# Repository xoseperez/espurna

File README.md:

# ESPurna Firmware

ESPurna ("spark" in Catalan) is a custom firmware for ESP32 and ESP8285/ESP8266 based smart switches, lights and sensors.
It uses the Arduino Core for ESP32 / ESP8266 frameworks and a number of 3rd party libraries.
This fork adds the [ESP32 and Beken BK72xx ports](#this-fork) and [a page per architecture](#architectures) with the boards run on it; the badges right below refer to the original upstream project.

<br />

---

## This fork

This fork is maintained by **@igorufox**. ESPurna itself is the work of Xose Pérez (**@xoseperez**), Max Prokhorov (**@mcspr**) and the upstream contributors, credited below.

It lives in the [`esp32-port`](https://github.com/igorufox/espurna/tree/esp32-port) branch: three architectures from the same source, a few generic images per chip instead of per-board builds (the board is picked after flashing, see [Picking the board](#picking-the-board)), and updates from the GitHub releases in the WebUI.

- **ESP8266 / ESP8285** (Arduino core 3.1.2, NONOS SDK 3.0.5): four generic images instead of the 216 per-board builds, a two-step update through a mini image on 1 MB boards, lwIP and module memory tuned so that the WebUI and uploads fit in the heap, AC mains wall-switch inputs; builds in [`code/platformio.ini`](code/platformio.ini), [esp8266/README.md](esp8266/README.md);
- **ESP32** (Arduino-ESP32 core 3 / ESP-IDF 5 via [pioarduino](https://github.com/pioarduino/platform-espressif32), PlatformIO Core 6.2 or newer; Matter On/Off plugs; safeboot flash layout with Tasmota's offsets, [`code/esp32_4mb_safeboot.csv`](code/esp32_4mb_safeboot.csv), and an own safeboot image, [`code/safeboot-app`](code/safeboot-app)), code under [`code/espurna/arch/esp32`](code/espurna/arch/esp32), [esp32/README.md](esp32/README.md);
- **Beken BK7231N** (Tuya CB2S / CB3S / CBU and compatible modules, Tuya or Quectel bootloader) through [LibreTiny](https://docs.libretiny.eu/), Matter On/Off plugs, code under [`code/espurna/arch/beken`](code/espurna/arch/beken), builds in [`code/platformio_beken.ini`](code/platformio_beken.ini), [beken/README.md](beken/README.md).

How updates work on each chip, the releases and CI: [docs/updates.md](docs/updates.md).

### Architectures

One source, three architectures; every one has a page with its images, the boards run on it, their pages and its
nuances. Boards run on the generic image of their chip; pins come from the device template (*ADMIN → Device Template*)
or the settings, not from the build.

| Architecture | Images | Boards run on it | Page |
|--------------|--------|------------------|------|
| **ESP8266 / ESP8285** | `esp8266-1m`, `-1m-light`, `-1m-sensor`, `-4m` (+ the mini) | Sonoff Basic, Sonoff Mini R1/R2, Moes MS-104B, HW-622, LC-Tech ESP-12F relay x2 and x4 | [esp8266/README.md](esp8266/README.md) |
| **ESP32** | `esp32-matter`, `esp32-matter-nspanel` (+ the safeboot) | LC-Tech ESP32 relay x2, Sonoff MINIR4, Sonoff NSPanel | [esp32/README.md](esp32/README.md) |
| **Beken BK7231N** | `beken-matter` (+ two UART images) | Tuya TYWRA-RF (CB3S), Tuya 4-gang (CBU), Sparkleiot Mini (XH-CB2S), in-wall relay 86-TDQ (CB2S), MOES MS-104B Matter (CBU) | [beken/README.md](beken/README.md) |

How updates work on each chip, the releases and CI: [docs/updates.md](docs/updates.md).

### Download

Every push to `esp32-port` is built by [GitHub Actions](https://github.com/igorufox/espurna/actions/workflows/esp32.yml) and published as one [release](https://github.com/igorufox/espurna/releases/latest) for all chips, tag `esp32-YYMMDD-<sha7>`; the newest 5 are kept. The same files with their SHA-256 are listed in [`firmware.json`](https://igorufox.github.io/espurna/firmware.json) on GitHub Pages, which the WebUI reads. The latest image is always at `https://github.com/igorufox/espurna/releases/latest/download/espurna-<image>...`, e.g. [espurna-esp32-matter.bin](https://github.com/igorufox/espurna/releases/latest/download/espurna-esp32-matter.bin). Which image and how to flash it the first time: the page of the architecture.

### Updating

WebUI, *ADMIN*, OTA: *Upgrade* with a file as before, or *From GitHub*, *Show releases*: the kept releases with the files of the image the board runs, *Install*. The WebUI lists the steps ahead and goes through them by itself; the board restarts during the install.

- **ESP32**: through the safeboot, which downloads the image's `.bin` itself and writes its ESPurna part; two-slot boards are migrated on the way.
- **Beken**: the browser uploads `espurna-beken-matter.bin`, the board writes the part for its bootloader; on 2 MiB Tuya boards in up to three uploads of the same file, because the Matter code lives in the update partition ([how](docs/updates.md#2-mib-tuya-boards-where-matter-lives)).
- **ESP8266**: one upload on the 4 MB layout; on 1 MB boards the mini first, which downloads the compressed full image from GitHub Pages.

Details, limits and what happens when an install stops half-way: [docs/updates.md](docs/updates.md).

### Picking the board

WebUI, *ADMIN*, *Device Template*: type the name (e.g. `sonoff mini`, `shelly 1pm`, `ms-104b`) and *Apply*. The list is downloaded by the browser at that moment from [templates.blakadder.com](https://templates.blakadder.com) (Tasmota templates, ESP8266 / ESP32), [OpenBeken](https://openbekeniot.github.io/webapp/devicesList.html) (Beken) and [igorufox/espurna-devices](https://github.com/igorufox/espurna-devices) (*ESPurna devices*, results marked `[github]`); nothing is stored here. AC mains wall switches are marked afterwards on the RELAYS panel, per button. Your own board: [add a template](https://templates.blakadder.com/new.html) to the Tasmota list, the `devices.json` of [openbekeniot/webapp](https://github.com/openbekeniot/webapp) for Beken, or an entry of espurna-devices.

**ESPurna devices.** [`devices.json`](https://github.com/igorufox/espurna-devices) holds every ESP8266 board of [`hardware.h`](code/espurna/config/hardware.h) (generated by [`code/scripts/boards_to_devices.py`](code/scripts/boards_to_devices.py), most of them not verified on hardware since the move to generic images) and the no-name boards that are in no other list, such as the [CBU 4-gang module](beken/cbu-4gang.md) and the [Sparkleiot Mini](beken/sparkleiot-mini.md). Another list: the `webTplUrl` setting, *Own device list* in the same panel. A board set up by hand is turned into an entry with *Export this device as a template*: only relay / button / LED / UART / RF pins, button actions and the board names are taken, never Wi-Fi, MQTT, passwords or topics, and only those keys are ever applied from the list.

### Build from source

```
cd code
pio run -e esp8266-1m                                # ESP8266, see esp8266/README.md
pio run -d safeboot-app                              # ESP32: the safeboot first, then
pio run -c platformio_esp32.ini -e esp32-generic
py -3 -m platformio run -c platformio_beken.ini -e beken-bk7231n   # Beken
```

Details per architecture on its page.

---

# Original ESPurna README

Everything below is the upstream [xoseperez/espurna](https://github.com/xoseperez/espurna) README and describes ESP8266 builds.

## Collaborators (upstream)

Since November 2018, Max Prokhorov (**@mcspr**) is also actively working as a collaborator of the project. 

## Contributors (upstream)

**Without your help this project would not be possible**. I (**@xoseperez**) simply can't spend all the time I wish on ESPurna but luckily I receive a lot of contributions, bug fixes, enhancement suggestions,... from people all around the world. I would like to thank each and every one of you. The [contributors](https://github.com/xoseperez/espurna/graphs/contributors) page shows the ones that have done a PR in the past, but I also get contributions in the issues, by email or via the [gitter ESPurna channel](https://gitter.im/tinkerman-cat/espurna), those I also want to thank.

**Thank you all very much**.

## Notice

> Ladies and gentlemen in the embedded world, use [PlatformIO](https://platformio.org/). If I could offer you only one tip for the future, [PlatformIO](https://platformio.org/) would be it.

> Please use the [gitter ESPurna channel](https://gitter.im/tinkerman-cat/espurna) for support and questions, you have better chances to get fast answers from me or other ESPurna users. Open an issue here only if you feel there is a bug or you want to request an enhancement. Thank you.

> Process of building ESPurna from source is documented in the Wiki:  
[Using PlatformIO IDE for VSCode](https://github.com/xoseperez/espurna/wiki/Build-and-update-from-Visual-Studio-Code-using-PlatformIO)  
[Using PlatformIO CLI](https://github.com/xoseperez/espurna/wiki/PlatformIO)  
[Using Arduino IDE](https://github.com/xoseperez/espurna/wiki/ArduinoIDE)  

## Features

* *KRACK* vulnerability free (when built with Arduino Core >= 2.4.0)
* Support for **multiple ESP8266-based boards** ([check list](https://github.com/xoseperez/espurna/wiki/Hardware))
* Power saving options
* Wifi **AP Mode** or **STA mode**
    * Supports static IP
    * Up to 5 different networks can be defined
    * Scans for strongest network if more than one defined (also available in web UI)
    * Handles correctly multiple AP with the same SSID
    * Defaults to AP mode (also available after double clicking the main button)
    * Support for **WPS** and **Smart Config** (not available in default builds)
* Network visibility
    * Supports mDNS (service reporting and metadata) both server mode and client mode (.local name resolution)
    * Supports NetBIOS, LLMNR and Netbios (when built with Arduino Core >= 2.4.0) and SSDP (experimental)
* Switch management
    * Support for **push buttons** and **toggle switches**
    * Support for **digital** and [**analog**](https://en.wikipedia.org/wiki/Resistor_ladder) buttons
    * Configurable **status on boot** per switch (always ON, always OFF, same as before or toggle)
    * Support for **pulse mode** per switch (normally ON or normally OFF) with configurable time
    * Support for **relay synchronization** (all equal, only one ON, one and only on ON)
    * Support for **MQTT groups** to sync switches between devices
    * Support for **delayed ON/OFF**
    * Support for **latched relays**
* **MQTT** enabled
    * **SSL/TLS support** (not on regular builds, see [#64](https://github.com/xoseperez/espurna/issues/64) and [#1465](https://github.com/xoseperez/espurna/issues/1465))
    * Switch on/off and toggle relays, group topics (sync relays between different devices)
    * Report button event notifications
    * Enable/disable pulse mode
    * Change LED notification mode
    * Remote reset the board
    * Fully configurable in webUI (broker, user, password, QoS, keep alive time, retain flag, client ID)
* **Scheduler** to automatically turn on, off or toggle any relay at a given time and day, also change light intensity for dimmers
* **Alexa** integration using the [FauxmoESP Library](https://bitbucket.org/xoseperez/fauxmoesp)
* [**Google Assistant**](http://tinkerman.cat/using-google-assistant-control-your-esp8266-devices/) integration using IFTTT and Webhooks (Google Home, Allo)
* [**Domoticz**](https://domoticz.com/) integration via MQTT
* [**Home Assistant**](https://home-assistant.io/) integration
    * Support for switches (on/off)
    * Support for lights (color, brightness, on/off state)
    * Supports MQTT auto-discover feature (switches, lights and sensors)
    * Integration via MQTT Discover or copy-pasting configuration code
* [**InfluxDB**](https://www.influxdata.com/) integration via HTTP API
* [**Prometheus**](https://prometheus.io/) metrics integration via HTTP API
* [**Thingspeak**](https://thingspeak.com/) integration via HTTP API (HTTPS available for custom builds)
* **Sonoff RF Bridge** support
    * Multiple virtual switches (tested with up to 16)
    * MQTT-to-RF two-way bridge (no need to learn codes)
    * Support for [https://github.com/Portisch/RF-Bridge-EFM8BB1](https://github.com/Portisch/RF-Bridge-EFM8BB1) custom firmware
    * Support for [direct control of the encoder/decoder bypassing the EFM8BB1](https://github.com/xoseperez/espurna/wiki/Hardware-Itead-Sonoff-RF-Bridge---Direct-Hack)
* Support for [different **sensors**](Sensors)
    * Environment
        * **DHT11 / DHT12 / DHT22 / DHT21 / AM2301 / Itead's SI7021**
        * **BMP180**, **BMP280** and **BME280** pressure, humidity (BME280) and temperature (BMP280 & BME280) sensor by Bosch
        * **BME680** pressure, humidity, temperature and gas sensor by Bosch with support for Bosch's proprietary library BSEC for accurate Indoor Air Quality (IAQ) monitoring (⚠️ [learn more](https://github.com/xoseperez/espurna/wiki/Sensors#bme680-environmental-sensor))
        * **TMP35** and **TMP36** analog temperature sensors
        * **MAX6675** temperature sensor
        * **NTC** temperature sensors
        * **SI7021** temperature and humidity sensor
        * **SHT3X** temperature and humidity sensor over I2C (Wemos shield)
        * **AM2320** temperature and humidity sensor over I2C
        * **Dallas OneWire sensors** like the DS18B20
        * **MHZ19** CO2 sensor
        * **T6613** CO2 sensor
        * **MICS2710** CO2 & NO2 sensor
        * **MICS5525** CO & CO2 sensor
        * **SenseAir S8** CO2 sensor
        * **PMSX003/PMS5003T/ST** dust sensors
        * **SDS011** dust sensor
        * **BH1750** luminosity sensor
        * **GUVAS12SD** UV sensor
        * **VEML6075** UV Sensor
        * **EZO pH Circuit**
        * **Geiger counter** by RH Electronics
        * **HC-SR04**, **SRF05**, **SRF06**, **DYP-ME007**, **JSN-SR04T** & **Parallax PING)))™** distance sensors
        * **VL53L1X** distance sensor
        * **MAX6675** K-thermocouple-to-digital converter
        * **NTC** thermistor
        * **LDR** light-dependent resistor sensor
    * Power monitoring
        * **HLW8012** using the [HLW8012 Library](https://bitbucket.org/xoseperez/hlw8012) (Sonoff POW)
        * **CSE7766** and **CSE7759B** power monitor chips
        * **HJL-01** and **BL0937** power monitor chips
        * Non-invasive **current sensor** using **internal ADC** or **ADC712** or **ADC121** or **ADS1015** / **ADS1115**
        * **V9261F** power monitor chip
        * **PZEM0004T**  power monitor board
        * **ECH1560** power monitor chip
        * **ADE7953** power monitor chip
    * Raw **analog** and **digital** sensors
    * Simple **pulse counter** with **event triggering** option
    * Support for (almost) any UART based sensor via the **UART-to-MQTT module**
    * Support for different units (Fahrenheit or Celsius, Watts or Kilowatts, Joules or kWh)
* Support for LED lights
    * MY92XX-based light bulbs and PWM LED strips (dimmers) up to 5 channels (RGB, cold white and warm white, for instance)
    * Support for CCT lights
    * RGB and HSV color codes supported
    * Manage channels individually
    * Temperature color supported (in [mired](https://en.wikipedia.org/wiki/Mired) and [kelvin](https://en.wikipedia.org/wiki/Color_temperature)) via MQTT / REST API
    * Flicker-free PWM management
    * Soft color transitions
    * Color synchronization between light using MQTT
    * Option to have separate switches for each channel
* Support for simple 433MHz RF receivers
* Support for UART-to-MQTT bidirectional bridge
* Fast asynchronous **HTTP Server** and cool **Web User Interface**
    * Configurable port
    * Basic authentication
    * Web-based configuration
    * Relay switching and sensor data from the web interface
    * Handle color, brightness, and white/warm channels for lights
    * Websockets-based communication between the device and the browser
    * Backup and restore settings option
    * Upgrade firmware from the web interface
    * Works great behind a [secured reverse proxy](http://tinkerman.cat/secure-remote-access-to-your-iot-devices/)
* **REST API** (enable/disable from web interface)
    * GET and PUT relay status (including pulses)
    * Change light color (for supported hardware)
    * GET sensor data (power, current, voltage, temperature and humidity) depending on the available hardware
    * Works great behind a secured reverse proxy
* **RPC API** (enable/disable from web interface)
    * Remote reset the board
* **RPN Rules - on-device automation**
    * Relays on/off/toggle
    * Lights control
    * Publish / subscribe to MQTT
    * RF receiver integration
* **Over-The-Air** (OTA) updates even for 1Mb boards
    * Manually from PlatformIO or Arduino IDE
    * Automatic updates through the [NoFUSS Library](https://bitbucket.org/xoseperez/nofuss)
    * Update from web interface using pre-built images
* **Command line configuration**
    * Change configuration
    * Run special commands
* **Telnet support**
    * Enable/disable via the web UI
    * Shows debug info and allows to run terminal commands
* **NTP** for time synchronization
    * Supports worldwide time zones
    * Compatible with DST (based on [POSIX TZ variable](https://www.gnu.org/software/libc/manual/html_node/TZ-Variable.html) support)
* **Unstable system check**
    * Detects unstable system (crashes on boot continuously) and defaults to a stable system
    * Only WiFi AP, OTA and Telnet available if system is flagged as unstable
* Configurable LED notifications based on WiFi status, relays status or MQTT messages.
* Button interface
    * Click to toggle relays
    * Double click to enter AP mode (only main button)
    * Long click (>1 second) to reboot device (only main button)
    * Extra long click (>10 seconds) to go back to factory settings (only main button)
    * Specific definitions for touch button devices (ESPurna Switch, Sonoff Touch & T1)
* Configuration stored in different flash sectors to prevent data loss and corruption
* **Garland** Implementing garland using WS2812 leds
    * 12 animation modes (include start animation)
    * Web control for:
        * ON/OFF, brightness, speed
    * MQTT control:
        * ON/OFF, brightness, speed
        * Animation queue
        * Animation sequence

## Notices

---
> **2018-04-08**<br />
> Please use [gitter](https://gitter.im/tinkerman-cat/espurna) for support and questions, you have better chances to get fast answers by me or other ESPurna users. Open an issue here only if you feel there is a bug or you want to request an enhancement. Thank you.

---
> **2018-03-09**<br />
> Default branch in GitHub is now the development branch "dev".<br>
> The stable branch (the one used to create the [binary releases](https://github.com/xoseperez/espurna/releases)) is "[master](https://github.com/xoseperez/espurna/tree/master)".

---
> **2018-01-24**<br />
> This repository has been migrated from Bitbucket to GitHub. There were a number of reason to migrate the repository to GitHub. I like Bitbucket and I'm still using it for a lot of projects, but ESPurna has grown and its community as well. Some users have complain about Bitbucket not being enough community-focused. This change is mainly aimed to use a platform with greater acceptance on the open-source community and tools better suited to them (to you), like the possibility to contribute to the documentation in an easy way.
>
>What happened with all the info in Bitbucket? Well, most of it has been ported to GitHub, albeit with some quirks:
>
>* **Code** has, of course been migrated completely
>* **Issues** are all on GitHub already **but** all issues and comments show up as reported by me. The original reporter is referenced inside the body of the issue (or comment) with a link to his/her profile at Bitbucket and a link to his/her profile at GitHub if it happens to be the same username. I **suggest all reporters to subscribe to the issues they originally filed** (search for your BitBucket username to list them).
>* **Pull requests** historic has not been migrated. At the moment of the migration all pull-requests have been either merged or declined. Of course, those PR merged are in the code base, but the historic and comments in the PR pages will be lost.
>* **Documentation** it's on it way, first step will be to migrate existing wiki, maybe with a new TOC structure
>* **Watchers**, **Forks**, I'm afraid they are all gone. Visit the new repo home and click on the "Watch" button on the top right. And as you do it click also on the "Star" button too :)
>
>I apologize for any inconvenience this migration may have caused. I have decided to do it the hard way.

---
> **2018-01-11**<br />
> As of current version (1.12.0) ESPurna is tested using Arduino Core 2.3.0 and it's meant to be built against that version.

---
> **2017-08-26**<br />
> Since version 1.9.0 the default **MQTT topics for commands have changed**. They all now end with "/set". This means you will have to change your controller software (Node-RED or alike) to send messages to -for instance- "/home/living/light/relay/0/set". The device will publish its state in "/home/living/light/relay/0" like before.

---
> **2017-07-24**<br />
> Default flash layout changed in 1.8.3, as an unpredicted consequence devices will not be able to persist/retrieve configuration if flashed with 1.8.3 via **OTA** from **PlatformIO**. Please check issue [#187](https://github.com/xoseperez/espurna/issues/187).

---

## Contribute

There are several ways to contribute to ESPurna development. You can contribute to the repository by doing:

* Pull requests (fixes, enhancements, new features... are very welcome)
* Documentation (I reckon I'm bad at it)
* Testing (filing issues or help resolving them, they take a lot of time and sometimes I don't have the required hardware to test them all)

And of course you can always buy me a beer, coffee, tea,... via the donation button below.

## Documentation

For more information please refer to the [ESPurna Wiki](https://github.com/xoseperez/espurna/wiki).

## Supported hardware

Here is the list of supported hardware. For more information please refer to the [ESPurna Wiki Hardware page](https://github.com/xoseperez/espurna/wiki/Hardware), search for wiki pages starting with *Hardware-...*, or search throught [our build configuration files with hardware presets](https://github.com/xoseperez/espurna/blob/dev/code/espurna/config/hardware.h).

### Power monitoring devices

||||
|---|---|---|
||||
|**Blitzwolf BW-SHP6**|**[Blitzwolf BW-SHP2](https://github.com/xoseperez/espurna/wiki/Hardware-BLITZWOLF-BW-SHP2)**<br />(also by Coosa, Gosund, HomeCube, Teckin)|**Blitzwolf BW-SHP5**|
||||
|**[Power meters based on V9261F](https://github.com/xoseperez/espurna/wiki/Hardware-Generic-V9261F)**|**[Itead Sonoff POW](https://github.com/xoseperez/espurna/wiki/Hardware-Itead-Sonoff-POW)**|**[Itead Sonoff POW R2](https://github.com/xoseperez/espurna/wiki/Hardware-Itead-Sonoff-POW-R2)**|
||||
|**[Itead Sonoff S31](https://github.com/xoseperez/espurna/wiki/Hardware-Itead-Sonoff-S31)**|**Smartlife (NETVIP) Mini Smart Socket**|**Teckin SP20**|
||||
|**Digoo NX SP202**|**Vanzavanzu Smart WiFi Plug Mini**|**Hykker Smart Home Power Plug**|

### Embedded switches

||||
|---|---|---|
||||
|**[Itead Sonoff Basic (including R2 and R3)](https://github.com/xoseperez/espurna/wiki/Hardware-Itead-Sonoff-Basic)**|**[Itead Sonoff Dual/Dual R2](https://github.com/xoseperez/espurna/wiki/Hardware-Itead-Sonoff-Dual)**|**[Itead Sonoff TH10/TH16](https://github.com/xoseperez/espurna/wiki/Hardware-Itead-Sonoff-TH)**|
||||
|**[Electrodragon WiFi IOT](https://github.com/xoseperez/espurna/wiki/Hardware-Electrodragon-ESP-Relay-Board)**|**[OpenEnergyMonitor WiFi MQTT Relay / Thermostat](https://github.com/xoseperez/espurna/wiki/Hardware-OpenEnergyMonitor-Wifi-MQTT-Relay)**||
||||
|**[Itead Sonoff 4CH](https://github.com/xoseperez/espurna/wiki/Hardware-Itead-Sonoff-4CH)**|**[Itead Sonoff 4CH Pro](https://github.com/xoseperez/espurna/wiki/Hardware-Itead-Sonoff-4CH-Pro---R2)**||
||||
|**Alterco Shelly 1 / 1PM**|**Alterco Shelly 2 / 2.5**|**[Jan Goedeke Wifi Relay (NO/NC)](https://github.com/xoseperez/espurna/wiki/Hardware-Jan-Goedeke-Wifi-Relay-Board)**|
||||
|**[EXS Wifi Relay v3.1](https://github.com/xoseperez/espurna/wiki/Hardware-EXS-WiFi-Relay-v3.1)**|**EXS Wifi Relay v5.0**|**[Jorge García Wifi + Relays Board Kit](https://github.com/xoseperez/espurna/wiki/Hardware-Jorge-Garcia-Wifi-Relay-Board)**|
||||
|**Allnet ESP8266-UP-Relay**|**Bruno Horta's OnOfre**|**Luani HVIO**|

### Wall Sockets

||||
|---|---|---|
||||
|**[Itead S20](https://github.com/xoseperez/espurna/wiki/Hardware-Itead-S20)**|**[Itead S26](https://github.com/xoseperez/espurna/wiki/Hardware-Itead-S26)**|**[Neo Coolcam NAS WR01W](https://github.com/xoseperez/espurna/wiki/Hardware-NEO-COOLCAM-NAS-WR01W)**|
||||
|**[Maxcio W-US002S](https://github.com/xoseperez/espurna/wiki/Hardware-Maxcio-W-US002S)**|**[HEYGO HY02](https://github.com/xoseperez/espurna/wiki/Hardware-HEYGO-HY02)**|**[YiDian XS-SSA05](https://github.com/xoseperez/espurna/wiki/Hardware-YiDian-XS-SSA05)**|
||||
|**[WiOn 50055](https://github.com/xoseperez/espurna/wiki/Hardware-WiOn-50055)**|**[LINGAN SWA1](https://github.com/xoseperez/espurna/wiki/Hardware-LINGAN-SWA1)**|**HomeCube 16A**|
||||
|**[WorkChoice EcoPlug](https://github.com/xoseperez/espurna/wiki/Hardware-WorkChoice-EcoPlug)**|**[Bestek MRJ1011](https://github.com/xoseperez/espurna/wiki/Hardware-Bestek-MRJ1011)**|**Tonbux XS-SSA01**|
||||
|**Schuko Wifi Plug**|**Schuko Wifi Plug V2**|**[KMC 70011](https://github.com/xoseperez/espurna/wiki/Hardware-KMC-70011)**|
||||
|**[Xenon SM-PW702U](https://github.com/xoseperez/espurna/wiki/Hardware-Xenon-SM-PW-702U)**|**[Orvibo B25](https://github.com/xoseperez/espurna/wiki/Hardware-Orvibo-B25)**|**Oukitel P1**|
||||
|**[Tonbux XS-SSA06](https://github.com/xoseperez/espurna/wiki/Hardware-Tonbux-XS-SSA06)**|**Litesun LA-WF3**|**[Maxcio W DE-004](https://github.com/xoseperez/espurna/wiki/Hardware-Maxcio-W-DE004)**|
||||
|**[Hama WiFi Steckdose](https://github.com/xoseperez/espurna/wiki/Hardware-Hama-WiFi-Steckdose,-3.500W,-16A-(Article-Number-00176533))**|**GBLife RGBW Socket**||

### Wall switches

||||
|---|---|---|
||||
|**[Itead Sonoff Touch](https://github.com/xoseperez/espurna/wiki/Hardware-Itead-Sonoff-Touch)**|**[Itead Sonoff T1](https://github.com/xoseperez/espurna/wiki/Hardware-Itead-Sonoff-T1)**|**YJZK 1/2/3-gangs switch**|
||||
|**Gosund WS1 / KS-602S**|||

### Power strips

||||
|---|---|---|
||||
|**[Tonbux PowerStrip02](https://github.com/xoseperez/espurna/wiki/Hardware-Tonbux-Powerstrip02)**|**Fornorm Power Strip**|**[Zhilde ZLD-44EU-W/ZLD-64EU-W](https://github.com/xoseperez/espurna/wiki/Hardware-Zhilde-ZLD-64EU-W)**|

### Smart lights

||||
|---|---|---|
||||
|**[Itead Slampher](https://github.com/xoseperez/espurna/wiki/Hardware-Itead-Slampher)**|**[Arilux E27](https://github.com/xoseperez/espurna/wiki/Hardware-Arilux-E27)**|**[Itead Sonoff B1](https://github.com/xoseperez/espurna/wiki/Hardware-Itead-Sonoff-B1)**|
||||
|**[AI-Thinker Wifi Light / Noduino OpenLight](https://github.com/xoseperez/espurna/wiki/Hardware-AI-Thinker-AI-Light)**|**Authometion LYT8266**|**AG-L4**|
||||
|**Lohas 9W**|**Xiaomi Smart Desk Lamp**|**[iWoole LED Table Lamp](https://github.com/xoseperez/espurna/wiki/Hardware-IWOOLE_LED_TABLE_LAMP)**|
||||
|**[Itead Sonoff LED](https://github.com/xoseperez/espurna/wiki/Hardware-Itead-Sonoff-LED)**|**[Itead BN-SZ01](https://github.com/xoseperez/espurna/wiki/Hardware-Itead-BN-SZ01)**|**[Lombex LUX Nova 2 (white and color)](https://github.com/xoseperez/espurna/wiki/Hardware-Lombex-Lux-Nova)**|
||||
|**Arilux AL-LC01 (RGB)**|**Arilux AL-LC02 (RGBW)**|**[Arilux AL-LC06 (RGBWWCW)](https://github.com/xoseperez/espurna/wiki/Hardware-Arilux-AL-LC06)**|
||||
|**Arilux AL-LC11 (RGBWWW) & RF**|**[MagicHome LED Controller (1.0/2.x, also ZJ WFMN A/B11)](https://github.com/xoseperez/espurna/wiki/Hardware-Magic-Home-LED-Controller)**|**[Huacanxing H801/802](https://github.com/xoseperez/espurna/wiki/Hardware-Huacanxing-H80x)**|
||
|**[Muvit I/O MIOBULB001](https://github.com/xoseperez/espurna/wiki/Hardware-Muvit-IO-miobulb001)**|**[Lampi Battery Powered Smart Light](https://github.com/xoseperez/espurna/wiki/Hardware-Lampi-RGBWW-Battery-Powered-Smart-Light)**|

### Radio links / gateways

||||
|---|---|---|
||||
|**Tinkerman RFM69GW**|**[Itead Sonoff RF Bridge](https://github.com/xoseperez/espurna/wiki/Hardware-Itead-Sonoff-RF-Bridge)**|**[Itead Sonoff RF](https://github.com/xoseperez/espurna/wiki/Hardware-Itead-Sonoff-RF)**|

### Other devices

||||
|---|---|---|
||||
|**[Tonbux Mosquito Killer](https://github.com/xoseperez/espurna/wiki/Hardware-Tonbux-Mosquito-Killer)**|**Itead Sonoff IFAN02**|||

### Custom & Development boards

||||
|---|---|---|
||||
|**[Tinkerman ESPurna H](https://github.com/xoseperez/espurna/wiki/Hardware-Tinkerman-ESPurna-H)**||**[NodeMCU Lolin V3](https://github.com/xoseperez/espurna/wiki/Hardware-NodeMCU-Lolin)**|
||||
|**[Itead Sonoff SV](https://github.com/xoseperez/espurna/wiki/Hardware-Itead-SV)**|**[Itead 1CH Inching](https://github.com/xoseperez/espurna/wiki/Hardware-Itead-1CH)**|**[Itead Motor Clockwise/Anticlockwise](https://github.com/xoseperez/espurna/wiki/Hardware-Itead-Motor)**|
||||
|**[ManCaveMade ESP-Live](https://github.com/xoseperez/espurna/wiki/Hardware-ManCaveMade-ESPLive)**|**[Wemos D1 Mini Relay Shield](https://github.com/xoseperez/espurna/wiki/Hardware-Wemos-D1-Mini-Relay-Shield)**|**[Gizwits Witty Cloud](https://github.com/xoseperez/espurna/wiki/Hardware-Witty-Cloud)**|
||||
|**[IKE ESPike](https://github.com/xoseperez/espurna/wiki/Hardware-IKE-ESPike)**|**Pilotak ESP DIN**|**[Arniex Swifitch](https://github.com/xoseperez/espurna/wiki/Hardware-Arniex-Swifitch)**|
||||
|**[Heltec Touch Relay](https://github.com/xoseperez/espurna/wiki/Hardware-Heltec-Touch-Relay)**|**[Generic Relay v4.0](https://github.com/xoseperez/espurna/wiki/Hardware-Generic-Relay-v40)**|**[Generic RGBLed v1.0](https://github.com/xoseperez/espurna/wiki/Hardware-Generic-RGBLed-v10)**|
||||
|**[Generic DHT11 v1.0](https://github.com/xoseperez/espurna/wiki/Hardware-Generic-DHT11-v10)**|**[Generic DS18B20 v1.0](https://github.com/xoseperez/espurna/wiki/Hardware-Generic-DS18B20-v10)**|**[InterMitTech QuinLED 2.6](https://github.com/xoseperez/espurna/wiki/Hardware-QuinLED)**|
||||
|**Phyx ESP12 RGBW**|**[RH Electronics Geiger Counter](https://github.com/xoseperez/espurna/wiki/Geiger-Counter)**|**[Green ESP Relay](https://github.com/xoseperez/espurna/wiki/Hardware-Green-ESP8266-Relay)**|
||||
|**Foxel Lightfox Dual**|||

## License

Copyright (C) 2016-2019 by Xose Pérez (@xoseperez)

This program is free software: you can redistribute it and/or modify
it under the terms of the GNU General Public License as published by
the Free Software Foundation, either version 3 of the License, or
(at your option) any later version.

This program is distributed in the hope that it will be useful,
but WITHOUT ANY WARRANTY; without even the implied warranty of
MERCHANTABILITY or FITNESS FOR A PARTICULAR PURPOSE.  See the
GNU General Public License for more details.

You should have received a copy of the GNU General Public License
along with this program.  If not, see <http://www.gnu.org/licenses/>.

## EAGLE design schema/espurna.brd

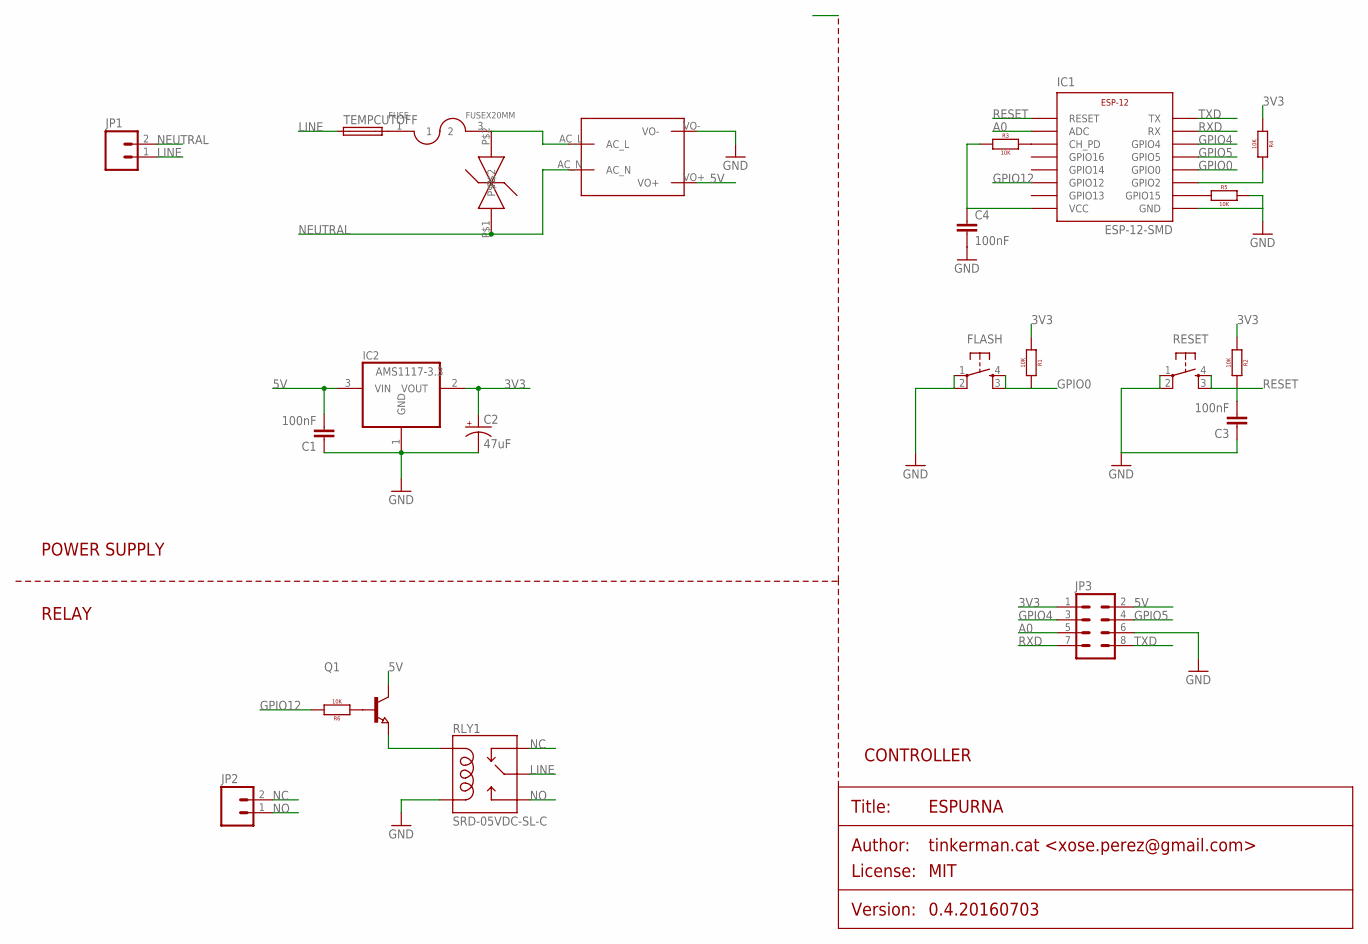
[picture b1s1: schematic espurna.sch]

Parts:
C1, C3, C4: 100nF; 0805
C2: 47uF; PANASONIC_C
FLASH: TACTILE_BUTTON_SMD; TACTILE-BUTTON-SMD
FUSE: FUSEX20MM; FUSE_5MM
IC1: ESP-12-SMD
IC2: AMS1117-3.3; SOT223
JP1, JP2: M02200MIL; SCREWTERMINAL-200MIL-2
JP3: M04X2; 2X4
Q1: NPN-TRANSISTOR_SOT23; SOT23
R1, R2, R3, R4, R5, R6: 10K; 0805
RESET: TACTILE_BUTTON_SMD; TACTILE-BUTTON-SMD
RLY1: SRD-05VDC-SL-C; SRD-5VDC-SL-C
TEMPCUTOFF: PICOFUSE
U$1: MAINS_CONVERTERS; HLK-PM01
VARISTOR: V18ZA2P

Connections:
3V3: C2.+, C4.1, IC1.VCC, IC2.2 (VOUT), JP3.1, R1.1, R2.1, R3.1, R4.1
5V: C1.2, IC2.3 (VIN), JP3.2, Q1.3 (C), U$1.VO+
A0: IC1.ADC, JP3.5
GND: C1.1, C2.-, C3.1, C4.2, FLASH.1 (SWA1), FLASH.2 (SWB1), IC1.GND, IC2.1 (GND), JP3.6, R5.2, RESET.1 (SWA1), RESET.2 (SWB1), RLY1.COIL2, U$1.VO-
GPIO0: FLASH.3 (SWB2), FLASH.4 (SWA2), IC1.GPIO0, R1.2
GPIO4: IC1.GPIO4, JP3.3
GPIO5: IC1.GPIO5, JP3.4
GPIO12: IC1.GPIO12, R6.2
LINE: JP1.1, RLY1.COMMON (MAIN), TEMPCUTOFF.1
unnamed: IC1.CH_PD, R3.2
unnamed: IC1.GPIO15, R5.1
unnamed: IC1.GPIO2, R4.2
unnamed: Q1.1 (B), R6.1
unnamed: FUSE.1, TEMPCUTOFF.2
unnamed: Q1.2 (E), RLY1.COIL1
unnamed: FUSE.3 (2), U$1.AC_L, VARISTOR.P$2
NC: JP2.2, RLY1.CLOSED (NC)
NEUTRAL: JP1.2, U$1.AC_N, VARISTOR.P$1
NO: JP2.1, RLY1.OPEN (NO)
RESET: C3.2, IC1.RESET, R2.2, RESET.3 (SWB2), RESET.4 (SWA2)
RXD: IC1.RX, JP3.7
TXD: IC1.TX, JP3.8

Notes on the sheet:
POWER SUPPLY
RELAY
CONTROLLER

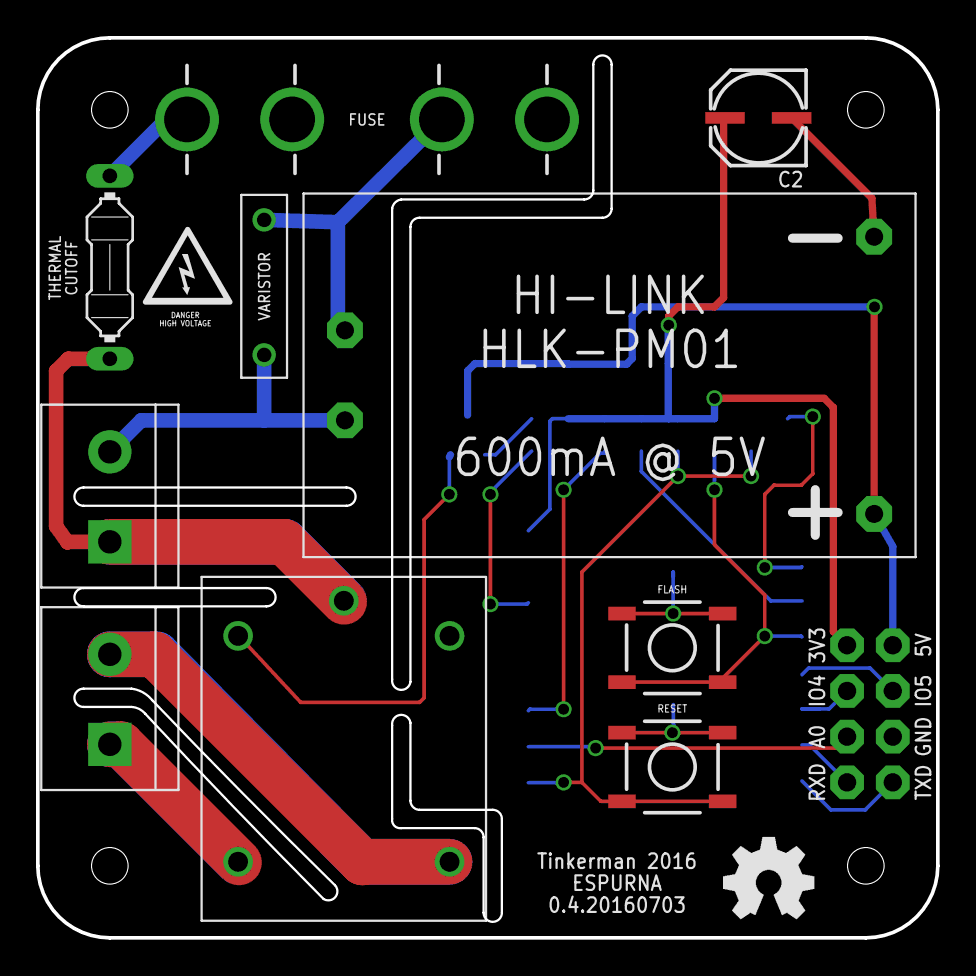
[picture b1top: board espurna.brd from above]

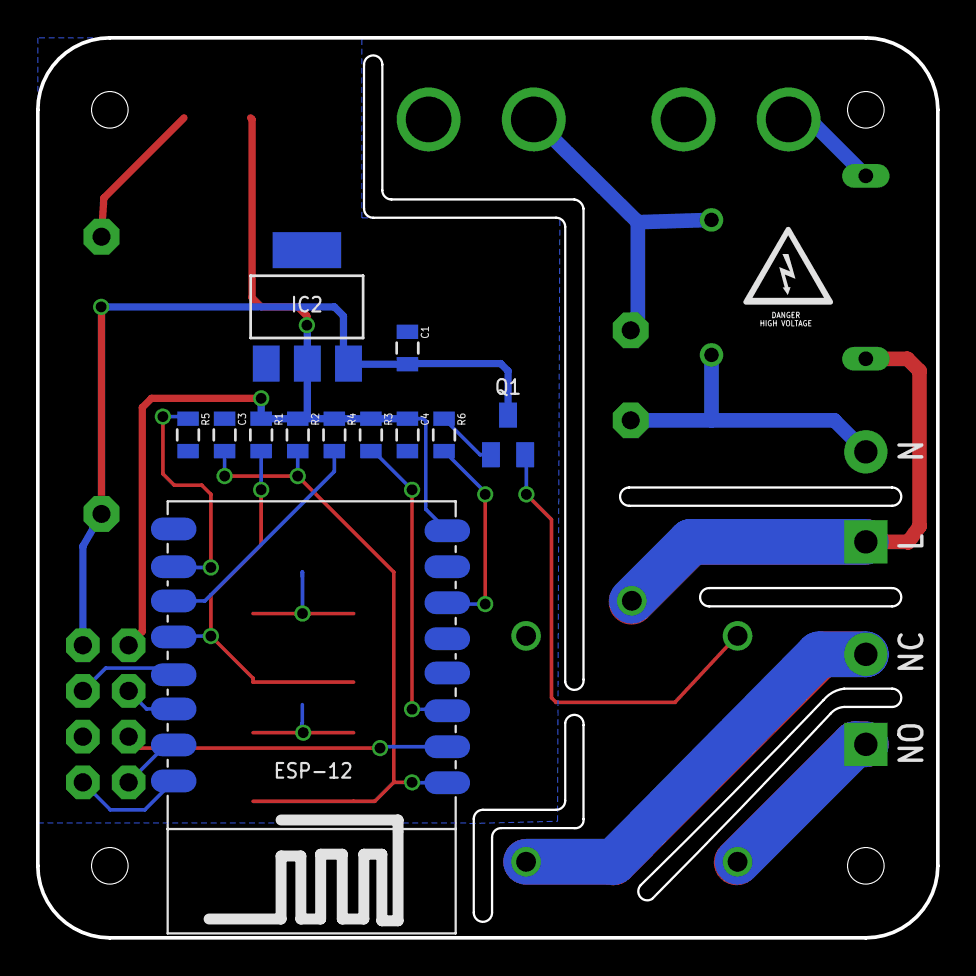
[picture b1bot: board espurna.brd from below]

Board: 2 copper layers, 50.0 x 50.0 mm, 23 parts (12 on the bottom side), 22 nets.

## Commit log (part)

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2024-02-08 dallas: do not wait until value() to report errors
    sensor loop assumes value(index) value is ok
    ref. #2543
    move all checks to pre(), value() returns pre-read value
    - tick() and pre() are allowed to fail specific device
    - pre() would fail the sensor if any of devices fail
    - value(index) is never reached unless tick() and pre() succeed
2024-02-08 dallas: fix device struct initialization
2025-01-21 Fixes HomeAssistant deprecation warning: Deprecated flag `color_mode` used in MQTT JSON light config , the `color_mode` flag is not used anymore and should be removed. ... This will stop working in H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
2025-03-05 libs(delimiter): split strings using the same utility function
2025-03-05 light(color): fix stateful parser api
2025-03-05 led: constexpr methods instead of temporaries
2025-03-05 test(sns): voltage magnitude should work
2025-03-05 test: expected vs. actual stringified
2025-03-05 test(unity): unused function
2025-03-05 test: fix unused / uninitialized warnings
2025-03-18 sns: experiment with magnitude persistent id
    ref. #2639
    global slot to identify specific sensor+num+type+slot combination
    for now, not used anywhere but terminal listing
2025-03-18 test(webui): enumerables spec extended
    minimum viable checks for ranges and manually created entries
    listen to and trigger events for span & select enumerable elements
2025-03-19 webui: rebuild blobs
2025-03-31 webui(build): missing builder readme.md
2025-03-31 webui(build): through2 -> node:stream Transform
    drop local dependency on through2 in favour of node:stream
    but, still ensure that things work for gulp-style File streams
2025-03-31 webui(build): pipeline instead of pipe
    ref.
    https://github.com/gulpjs/gulp/issues/2812
    https://nodejs.org/en/learn/modules/how-to-use-streams#how-to-operate-with-streams
    https://nodejs.org/en/learn/modules/how-to-use-streams#pipeline
    while the gulp issue refers to this as a workaround, this is actually the
    proper way to handle streams, merging streams and applying transformations
2025-03-31 webui(build): include vitest runner
2025-03-31 webui(build): lint & test imported on-demand
    minor speed-up when just building .html & .mjs
2025-04-01 webui(build): allow both gzip and br in the builder
    - switch to 'br' by default. convert relevant file references in the web.cpp
    .h -> .ipp and drop compression type from the filename
    'webui_content_encoding' string to help out the server
    - build options now include both minification and compression type
    - make sure output file syntax is valid when opening it standalone
2025-04-02 webui(server): remove ws & web internal settings references to external modules
    - provide 'prepend' option for ws callbacks, in addition to current 'append'
    - move unintentional adminpass check under normal callbacks, do not
    break the on_keychecks iteration when adminpass key is present
    - move key checks to their respective modules; reference existing key objects
2025-04-02 webui(ws): try to contain wsSend to the queue callback
    - 'log' payload nesting reduced, just one element (for now)
    - move terminal and ws logger into ws helper classes
    - 'manual' callback mode to simply allow for ws send window
    by using slightly more complicated loop w/ queue checks, though
2025-04-03 webui(ws): proper type of the callback container element
    lists refer to plain funcs, std::func only applies to a single callback
    namespace things yet again to fix the original implementation discrepancy
2025-04-03 webui(ws): cache log object reference
2025-04-03 webui(build): adjust mtime based on inline-source
    consistent datetime value when rebuilding from the same source
2025-04-04 build(deps): bump vite from 6.2.4 to 6.2.5 in /code
    Bumps [vite](https://github.com/vitejs/vite/tree/HEAD/packages/vite) from 6.2.4 to 6.2.5.
    - [Release notes](https://github.com/vitejs/vite/releases)
    - [Changelog](https://github.com/vitejs/vite/blob/v6.2.5/packages/vite/CHANGELOG.md)
    - [Commits](https://github.com/vitejs/vite/commits/v6.2.5/packages/vite)
    ---
    updated-dependencies:
2025-04-11 build(deps): bump vite from 6.2.4 to 6.2.6 in /code
    Bumps [vite](https://github.com/vitejs/vite/tree/HEAD/packages/vite) from 6.2.4 to 6.2.6.
    - [Release notes](https://github.com/vitejs/vite/releases)
    - [Changelog](https://github.com/vitejs/vite/blob/v6.2.6/packages/vite/CHANGELOG.md)
    - [Commits](https://github.com/vitejs/vite/commits/v6.2.6/packages/vite)
    ---
    updated-dependencies:
2025-04-14 webui(build): rollup circular dependency
    avoid sharing utility funcs through the main module
2025-04-14 webui(build): gulp html modifications should not happen in parallel
    Promise.all() does not handle array members in sequence
2025-04-14 webui(build): expect string or string[] as preset arg
2025-04-15 webui(build): support type=...;base64
    in case there are any unquotable or binary sources
    SCRIPT is an odd one per the spec, ignore type=...
    as it is describing how minification & bundling is done
2025-05-27 api: response-stream cannot read from unaligned mem
    names() references arbitrary stringview, not string
    internal cbuf does not use memcpy_P, but memcpy
2025-06-01 core: version bump
2025-06-01 ci(test): check output variables availability
    $build_date somehow gets lost at 'build', but not 'release'
    check other variables as well, using the same dependencies
2025-06-03 scripts: remove unused pre-commit
    there is only one branch, no need to sync readme
2025-06-07 Fixed retrieval of global settings so it returns global.ref() instead of indexed.ref() in button.cpp
2025-06-07 Revise the pixel cache update in ColorWave::move to iterate with size_t and decrement safely
2025-06-08 test(scripts): typing
2025-06-08 sns(am2320): directly use i2c buffer write
    removed in 6cd31f133a611153139cc633035b949359f3ccc3
2025-06-08 i2c: find* returns address on success
2025-06-19 i2c(internal): generic bit packing and casting
    common code when dealing with fixed size ints
    c++23 bit_cast when dealing with 'cpymem'-like ops
    compat header continues to use std number comparison since
    libstdcxx feature detection seem to rely on 'import' / 'include'
    (and 'bits/version.h' is not available in gcc4)
2025-06-20 settings(internal): allow foreach loop to stop
2025-06-20 settings(internal): naming & combine common move code
2025-06-25 ci(scripts): build.sh no longer used
2025-07-01 tspk(build): fallthrough warning
2025-07-01 sns(build): explicitly init strings, even when unused
    -Wmissing-field-initializers partial positive
    ref. https://gcc.gnu.org/bugzilla/show_bug.cgi?id=96868
2025-08-29 webui(build): remove mistakenly set src/*.html binary attribute
2025-09-08 ntp(debug): do not log server value twice
2025-09-08 pzem(modbus): reduntant templated code
    there is no need to specialization when doing common operations
    inject only the necessary params instead of the the whole body
2025-09-08 debug(uart): spurious unused function warning
    amends e76b67b355b75471b3b2a74b2a4f68959ad69505
2025-11-09 uart(debug): also disable rx when uart0 was configured w/o it
2025-11-09 led(pattern): refactoring
    w/ another -fsanitize=address hint, use separate objects instead of
    relying on pattern itself holding everything api *may* need
    combine pattern and preset patterns currently separate timers
    pattern container reworked to allow small-size optimization
    introduce a special '0,0' marker, repeating the whole pattern (instead
    of just one delay at the end)
2025-11-09 mqtt(debug): display empty message as 0 bytes
    since there is no quoting, should'nt mistake it for space(s)
2025-11-15 types(duration): micros & millis suffixes
    since underlying struct should be able to hold both magnitudes
    adjust tests & try to handle more cases
2025-11-16 relay(boot): skip hw gpio target status delay when soft resetting
    since pin state was retained and should immediately use rtcmem mask value
2025-11-24 system(boot): missing build flag checks
2025-11-26 Fix timer pointer dangling issue in _relayStatusNotify
2025-11-26 fixup! rpnrules status signature fix
2025-11-26 settings query
2025-11-27 pulse lingers w/o flags
2025-11-27 missing null check
2025-11-27 fixup! std::min oops
2025-11-28 missing pulse delay reset & fix mqtt forward
2025-11-28 previous iteration used relay.flags, fix to apply only when changing target
2025-11-28 .count() -> .any(), no need to count every bit when expecting .count() > 0
2025-11-28 relay(mqtt): common mqtt & api topics in flash
2025-11-28 relay(web): anonymous namespace
2025-11-29 test(build): expire old cache files before building
    should not be kept indefinitely, since sources may've been changed already
    ci cache dir is expected to only survive for the current build session,
    prefer similar behaviour for local build tests
2025-11-30 relay(callback): register & process active relays
2025-11-30 relay(callback): bitset operator[] returns reference
2025-12-02 relay(callback): revert to non-static instances
    wait until this is actually useful
2025-12-05 settings(embedis): sized reads & writes, function local state
    reduce the number of times one byte read()s are used
    since espXX implementation deals with memory blob most of the time,
    just return the data pointer to the buffer position and work w/ that
    internal rules for obj construction relaxed, fix implicit operator= deletion
    by using pointers instead of references. allow more default output objs
    prefer that reader / writer live only for the duration of the function
2025-12-05 test(embedis): missing index asserts
2025-12-05 settings(embedis): formatting
2025-12-09 relay(sync): sequential OFF / ON processing
    replace placeholder func w/ actual implementation
    generate two timers when necessary
    also fixes yet another instance of referencing
    relay[id].flags at the wrong time
2026-04-15 sch(sun): relative event handler typo
    ref. #2660
2026-04-15 webui(group): dynamically gather group element names
    don't store schema or cleanup prefixes on the group, lookup elements
    created or removed in -add / -del event handlers
    either every element name is used, or just the ones w/ cleanup class
    correctly check that bar prefix never appears in the data spec,
    only foo prefix does. arrayContaining was not used appropriately
2026-04-15 webui(build): bump rollup & rebuild blobs
    npm audit fix still manages to find something broken
2026-04-15 sch(sun): move event funcs to a separate module & add tests
    funcs are working on input and output arguments, not globals of the scheduler
    also avoid mixing up timestamp when figuring out next scheduled sunrise / sunset calc
2026-04-15 webui(build): eslint v10 & fix pattern matcher yet again
    revert absolute gulp paths back to relative ones for rules
    (still incomprehensible compared to other tools, but... preferable to separate configs)
    aux files moved to html/lib, avoid introducing glob anywhere near html/ root
    fixup another pipeline type mismatch, array not necessary
    more type fixes related to args parsing and error throws
    fixup switch case variables w/o block scope around them
2026-04-15 sch(sun): missing scheduler implementation file
2026-04-15 sch(sun): missing date time match update for calendar specs
2026-05-07 arch: implement orchestrated architecture for ESP32 and ESP8266 compatibility
    - moved platform-specific implementations to arch/esp8266 and arch/esp32
    - introduced orchestrator headers (*_orch.h) for architecture dispatching
    - resolved Windows naming conflicts for wifi.h
    - consolidated user_interface.h and pgmspace.h handling
    - fixed compilation and linking for both platforms
    - verified builds for ESP8266 (nodemcu-lolin) and ESP32
2026-05-20 fix(esp32): resolve ntp deadlock, loadavg underflow, vcc telemetry, ota space and webui render error
2026-05-21 Port heartbeat telemetry queue, settings, and conversion options to ESP32
2026-05-21 ha: Fix empty MQTT discovery payloads on AsyncMqttClient and preserve ESP8266 RAM optimization
    This commit fixes the Home Assistant MQTT discovery payloads being transmitted
    as empty strings ("") or garbage data under asynchronous MQTT transmission,
    while fully preserving and restoring the required memory caching design.
    1. Root Cause & Lifetime Bug:
    - Both ESP8266 and ESP32 platforms use AsyncMqttClient by default in Espurna.
    - AsyncMqttClient's publish() is non-blocking and does not duplicate payload

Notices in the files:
README.md:
License:
Copyright (C) 2016-2019 by Xose Pérez (@xoseperez)
This program is free software: you can redistribute it and/or modify
it under the terms of the GNU General Public License as published by
the Free Software Foundation, either version 3 of the License, or
(at your option) any later version.
This program is distributed in the hope that it will be useful,
but WITHOUT ANY WARRANTY; without even the implied warranty of
MERCHANTABILITY or FITNESS FOR A PARTICULAR PURPOSE.  See the
GNU General Public License for more details.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
schema/espurna.sch:
PROJECT_LICENSE: MIT
